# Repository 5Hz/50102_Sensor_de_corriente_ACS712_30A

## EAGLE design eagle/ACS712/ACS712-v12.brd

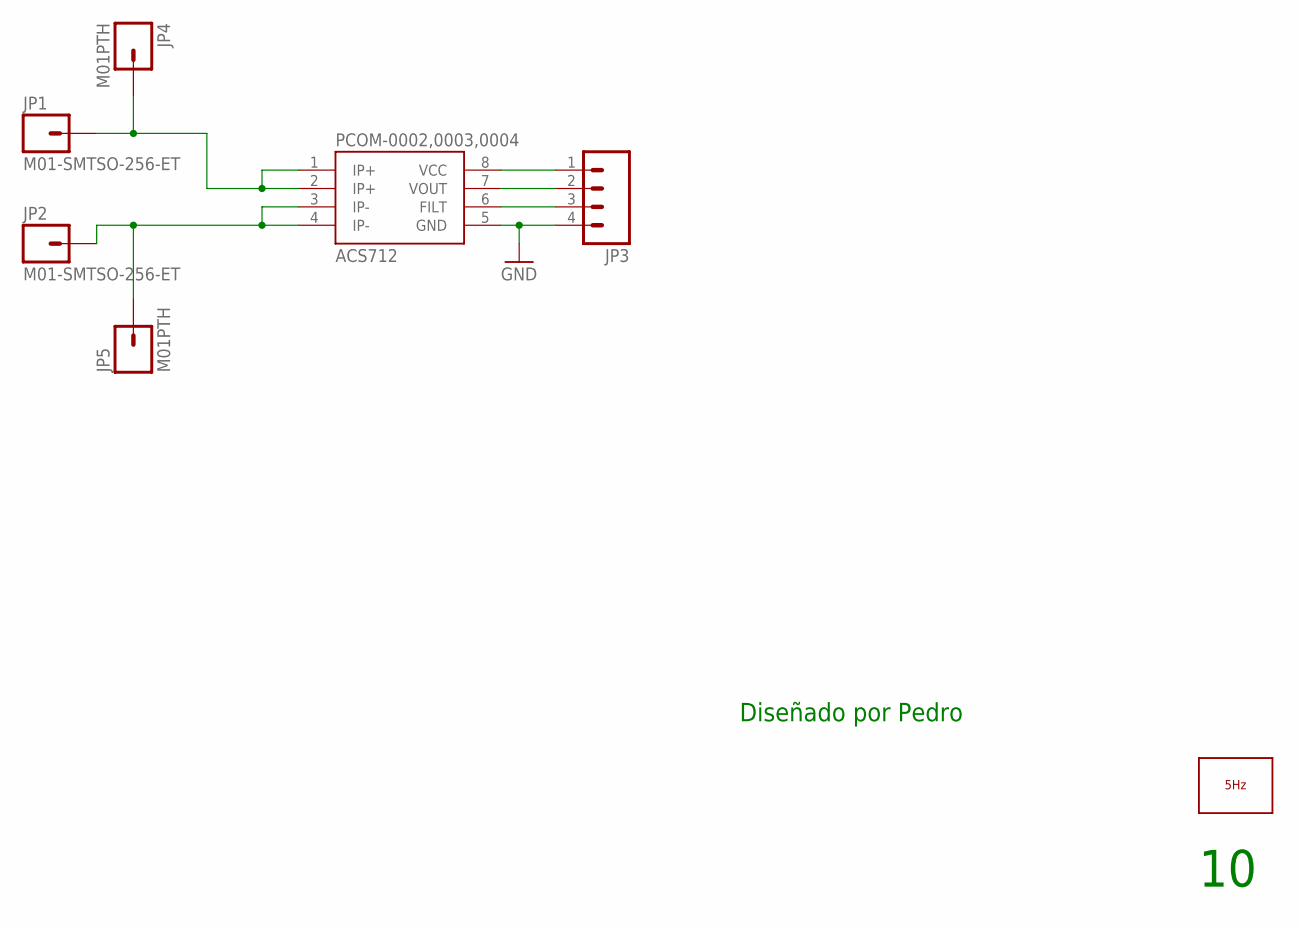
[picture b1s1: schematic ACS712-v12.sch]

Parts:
JP1, JP2: M01-SMTSO-256-ET; SMTSO-256-ET
JP3: M04PTH; 1X04
JP4, JP5: M01PTH; 1X01
LOGO1: LOGO_5HZ_H_10MM; 5HZ_LOGO_H_10MM
PCOM-0002,0003,0004: ACS712; SO08

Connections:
GND: JP3.4, PCOM-0002,0003,0004.5 (GND)
IP+: JP1.P$1, JP4.1, PCOM-0002,0003,0004.1 (IP+), PCOM-0002,0003,0004.2 (IP+)
IP-: JP2.P$1, JP5.1, PCOM-0002,0003,0004.3 (IP-), PCOM-0002,0003,0004.4 (IP-)
unnamed: JP3.1, PCOM-0002,0003,0004.8 (VCC)
unnamed: JP3.2, PCOM-0002,0003,0004.7 (VOUT)
unnamed: JP3.3, PCOM-0002,0003,0004.6 (FILT)

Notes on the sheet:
Diseñado por Pedro

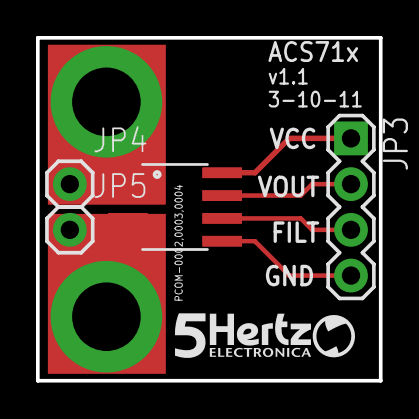
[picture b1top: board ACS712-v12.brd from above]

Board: 2 copper layers, 19.1 x 19.1 mm, 7 parts (0 on the bottom side), 6 nets.

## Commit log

2014-01-13 creación
